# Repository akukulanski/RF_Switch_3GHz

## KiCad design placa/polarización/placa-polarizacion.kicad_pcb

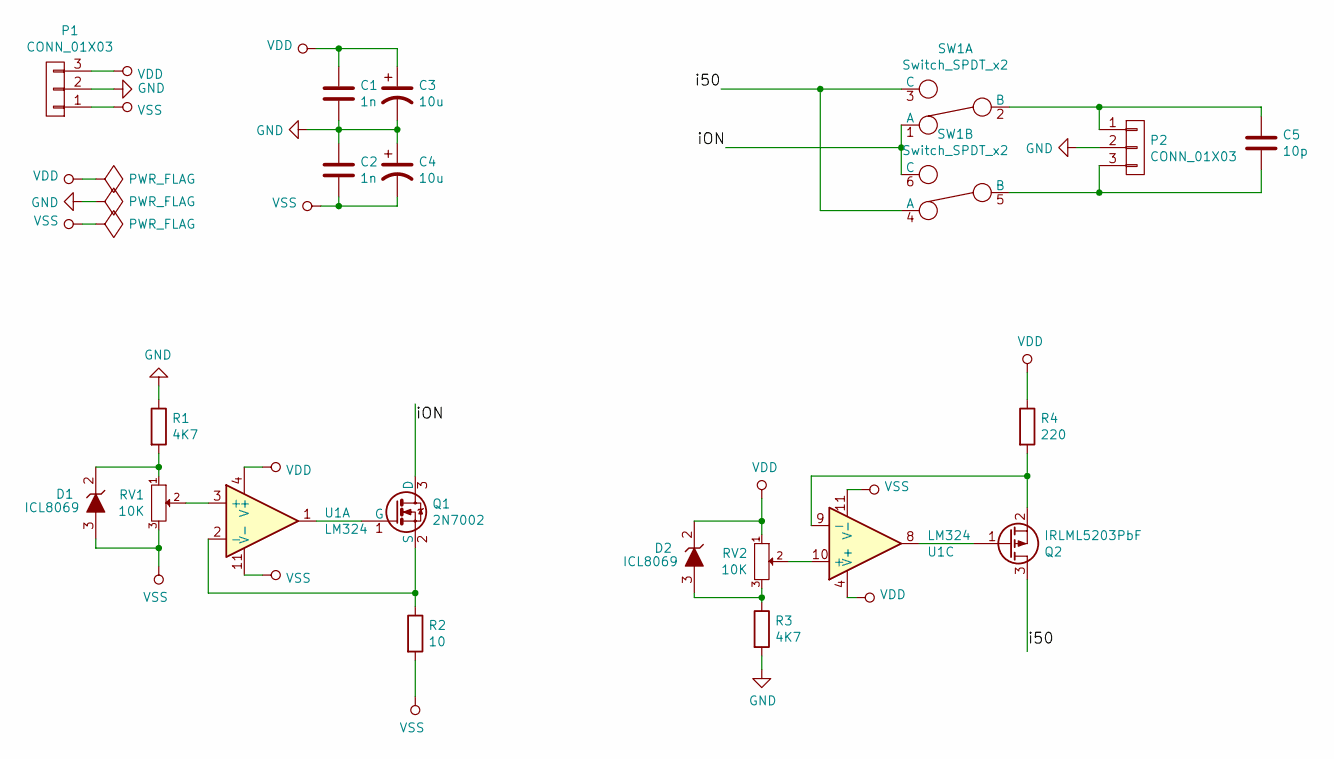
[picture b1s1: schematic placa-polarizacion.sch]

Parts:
C1, C2: 1n; C_Disc_D3_P2.5
C3, C4: 10u; C_Radial_D5_L11_P2
C5: 10p; C_Disc_D3_P2.5
D1, D2: ICL8069; TO-92_Inline_Narrow_Oval
P1, P2: CONN_01X03; Pin_Header_Angled_1x03
Q1: 2N7002; SOT-23
Q2: IRLML5203PbF; SOT-23
R1, R3: 4K7; Resistor_Horizontal_RM10mm
R2: 10; Resistor_Horizontal_RM10mm
R4: 220; Resistor_Horizontal_RM10mm
RV1, RV2: 10K; Potentiometer_Trimmer-Suntan-TSR-3386C
SW1: Switch_SPDT_x2; pulsador-doble-inversor-con-retencion
U1: LM324; DIP-14_W7.62mm_LongPads

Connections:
/i50: Q2.3 (D), SW1.3 (C), SW1.4 (A)
/iON: Q1.3 (D), SW1.1 (A), SW1.6 (C)
GND: C1.2, C2.1, C3.2, C4.1, P1.2, P2.2, R1.1, R3.2
unnamed: C5.1, P2.1, SW1.2 (B)
unnamed: C5.2, P2.3, SW1.5 (B)
unnamed: D1.2 (Z+), R1.2, RV1.1
unnamed: D2.3 (Z-), R3.1, RV2.3
unnamed: Q1.1 (G), U1.1
unnamed: Q1.2 (S), R2.1, U1.2 (-)
unnamed: Q2.1 (G), U1.8
unnamed: Q2.2 (S), R4.2, U1.9 (-)
unnamed: RV1.2, U1.3 (+)
unnamed: RV2.2, U1.10 (+)
VDD: C1.1, C3.1, D2.2 (Z+), P1.3, R4.1, RV2.1, U1.4 (V+)
VSS: C2.2, C4.2, D1.3 (Z-), P1.1, R2.2, RV1.3, U1.11 (V-)

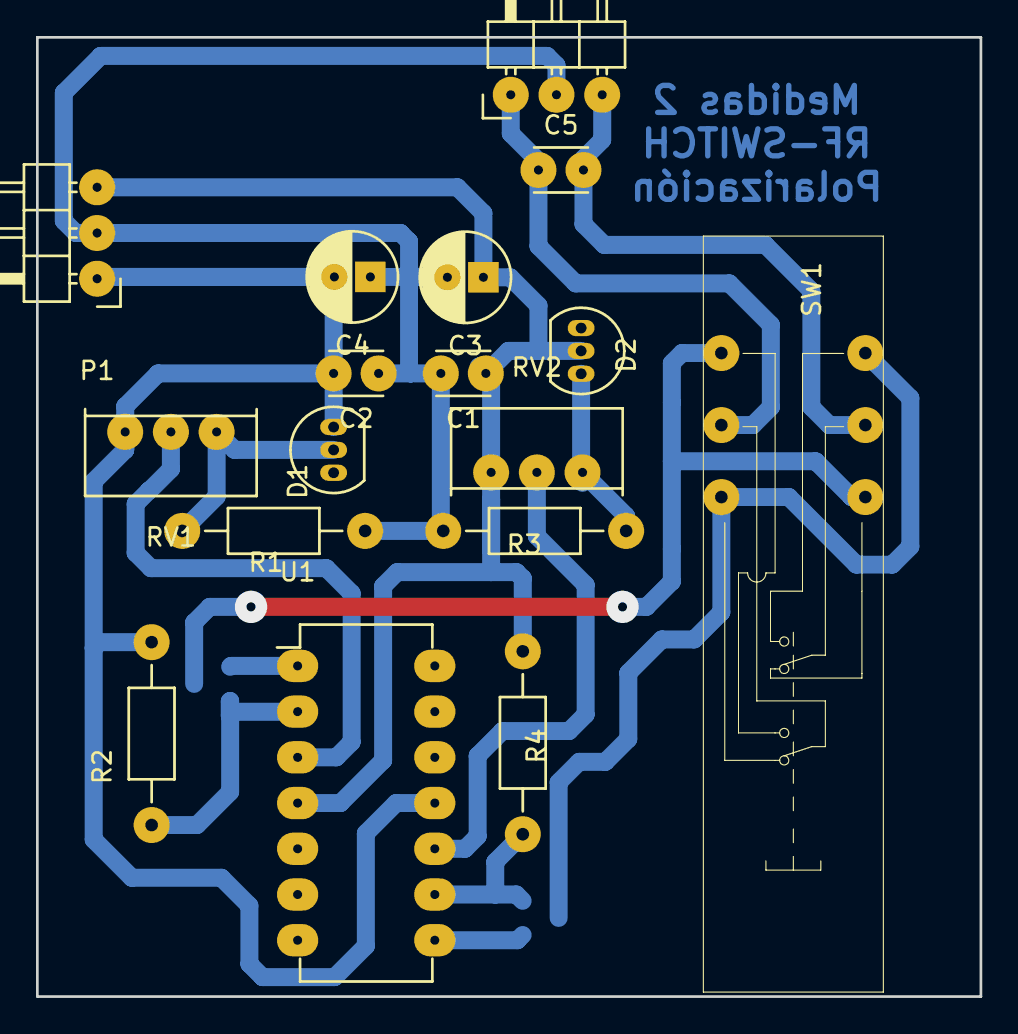
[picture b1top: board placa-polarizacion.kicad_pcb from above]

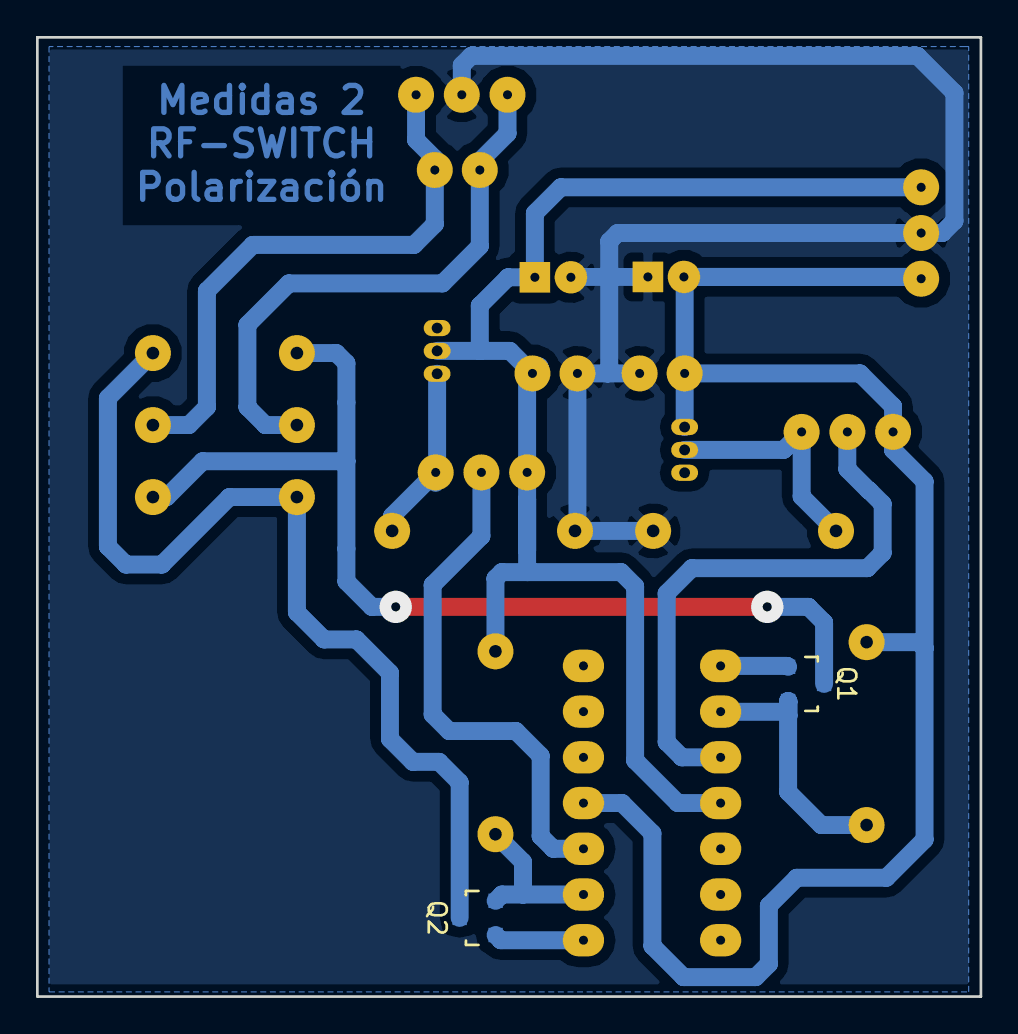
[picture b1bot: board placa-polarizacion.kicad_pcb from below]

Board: 2 copper layers, 52.4 x 53.3 mm, 19 parts (2 on the bottom side), 15 nets.

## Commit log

2016-07-14 Se agrega simulación con microstrip y carpeta con gráficos.
2016-07-14 Se agregan los gráficos con Microstrip
2016-08-08 Se empieza la ppt para el 13-08
2016-08-12 Actualización imagenes presentación
2016-08-12 ppt. Abrir con WPS ;)
2016-08-12 Nueva slide + correciones
2016-08-12 "Quedo 10 puntos!!!"
2016-09-06 Simulación con 2 choques en vez de R560 (Da todo igual). Circuito de Polarización en TINA (revisar. Falta poner alguna referencia de tensión)
2016-09-06 nada! pruebo que funcione integración con slack
2016-09-07 agrego archivo con ref de tensión + potes
2016-09-07 remuevo viejo
2016-09-07 archivo renombrado.
2016-09-08 Ancho de pista
2016-09-08 renombre de archivo
2016-09-15 Circuito en Altium (versión a fabricar) + PDFs a escala
2016-09-20 placa polarización, primer commit
2016-09-21 Revision de la placa
2016-10-18 Resultados primera medición
2017-12-20 entrega de informes, poster, etc.
2017-12-20 deleted file
